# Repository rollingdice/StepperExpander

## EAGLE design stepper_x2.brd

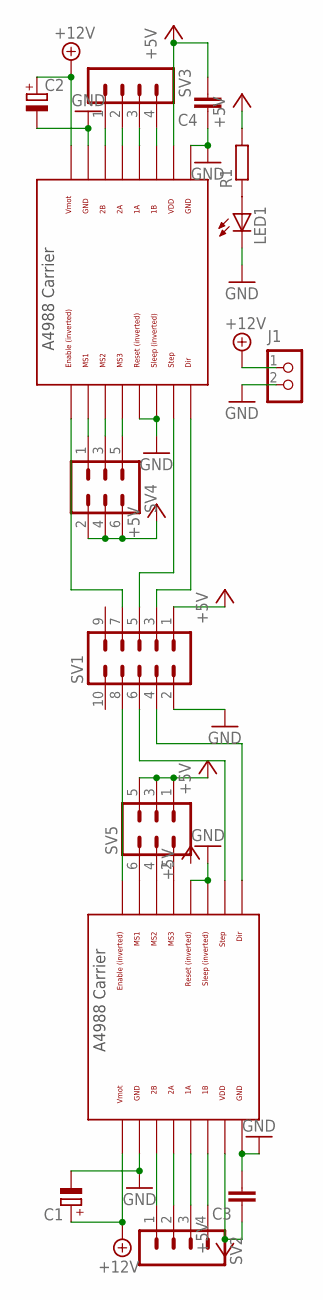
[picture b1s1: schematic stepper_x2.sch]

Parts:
C1, C2: CPOL-EU153CLV-0605; 153CLV-0605
C3, C4: C-EU025-030X050; C025-030X050
J1: CON_TERMINAL_BLOCK_02-5MM; TERMINAL_BLOCK_2P_5
LED1: LED5MM
R1: R-EU_0411/12; 0411/12
SV1: MA05-2
SV2, SV3: MA04-1
SV4, SV5: MA03-2
U$1, U$2: POLOLU_A4983CARRIER; A4988BREAKOUT

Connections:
+5V: C3.1, C4.2, R1.2, SV1.1, SV4.2, SV4.4, SV4.6, SV5.1, SV5.3, SV5.5, U$1.VDD, U$2.VDD
+12V: C1.+, C2.+, J1.1, U$1.VMOT, U$2.VMOT
GND: C1.-, C2.-, C3.2, C4.1, J1.2, LED1.K (C), SV1.2, U$1.GND, U$1.GND@0 (GND), U$1.RST, U$1.SLP (SLEEP), U$2.GND, U$2.GND@0 (GND), U$2.RST, U$2.SLP (SLEEP)
unnamed: LED1.A, R1.1
unnamed: SV1.7, U$1.EN
unnamed: SV1.3, U$1.DIR
unnamed: SV1.5, U$1.STEP
unnamed: SV2.4, U$2.1B
unnamed: SV2.3, U$2.1A
unnamed: SV2.2, U$2.2A
unnamed: SV2.1, U$2.2B
unnamed: SV3.4, U$1.1B
unnamed: SV3.3, U$1.1A
unnamed: SV3.2, U$1.2A
unnamed: SV1.8, U$2.EN
unnamed: SV1.4, U$2.DIR
unnamed: SV1.6, U$2.STEP
unnamed: SV3.1, U$1.2B
unnamed: SV4.5, U$1.MS3
unnamed: SV4.3, U$1.MS2
unnamed: SV4.1, U$1.MS1
unnamed: SV5.2, U$2.MS3
unnamed: SV5.4, U$2.MS2
unnamed: SV5.6, U$2.MS1

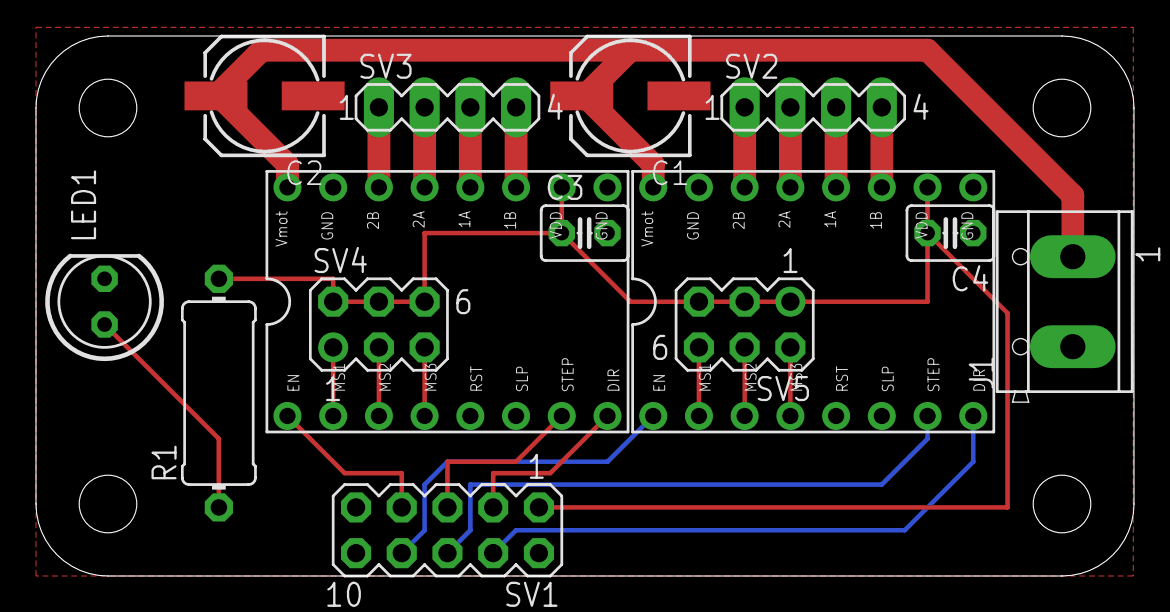
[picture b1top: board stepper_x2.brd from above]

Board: 2 copper layers, 61.0 x 30.0 mm, 14 parts (0 on the bottom side), 24 nets.

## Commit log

2016-05-11 Initial upload
